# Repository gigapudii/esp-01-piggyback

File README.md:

# ESP-01 USB programmer piggyback board
A small board that piggybacks on an ESP-01 module, and makes it easier for you to program the ESP8266 via a [USB-to-Serial board](https://i.imgur.com/NQs8db6.jpg).

## WHY
According to the datasheet of ESP8266, the GPIO-0 pin should be grounded for the microcontroller to be in programming mode. However, these cheap USB-to-Serial adaptors from China don't offer a way to make that connection.

If you want to use these adaptors, you would have to solder the connection yourself. This doesn't look very nice and it is not the only problem. After soldering the pins together, you wouldn't be able to use the ESP with the adaptor to run your software because the microcontroller will always be stuck in programming mode.

## HOW
My solution to this is this little board, that will sit between the ESP-01 and the USB-to-Serial board. Using the jumper, one can switch between programming and normal mode easily without soldering any pins together.

## Components
* [ESP-01 piggyback PCB](https://oshpark.com/shared_projects/A7Z1UCeJ)
* 3-pin male header
* Pin jumper

## Media
* [Demo video](https://youtu.be/fUgga0gxCAw)

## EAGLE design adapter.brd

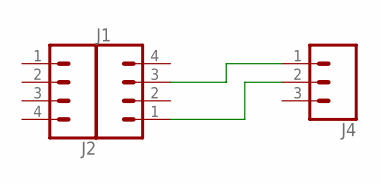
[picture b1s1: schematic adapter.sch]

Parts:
J1, J2: CONN_04LOCK; 1X04_LOCK
J4: CONN_03; 1X03

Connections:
unnamed: J1.3, J4.1
unnamed: J1.1, J4.2

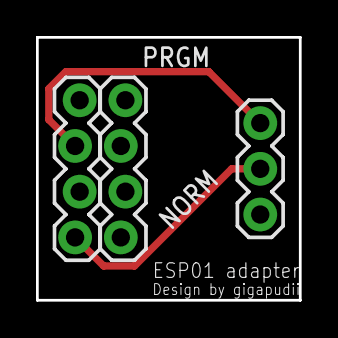
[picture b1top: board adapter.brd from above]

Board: 2 copper layers, 14.6 x 14.6 mm, 3 parts (0 on the bottom side), 2 nets.

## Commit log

2018-03-27 Add readme
    Add initial version of readme
2018-03-27 Add adaptor pcb design files
    Pcb design files made in Eagle CAD
2018-03-27 Add board pictures and oshpark link
2018-03-27 Place pictures in the same line
2018-03-27 Change from ESP8266 to ESP-01
    It's good to be more specific, since I used the ESP-01 module

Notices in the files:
parts and their libraries:
SparkFun-Connectors: Licensing: Creative Commons ShareAlike 4.0 International - https://creativecommons.org/licenses/by-sa/4.0
